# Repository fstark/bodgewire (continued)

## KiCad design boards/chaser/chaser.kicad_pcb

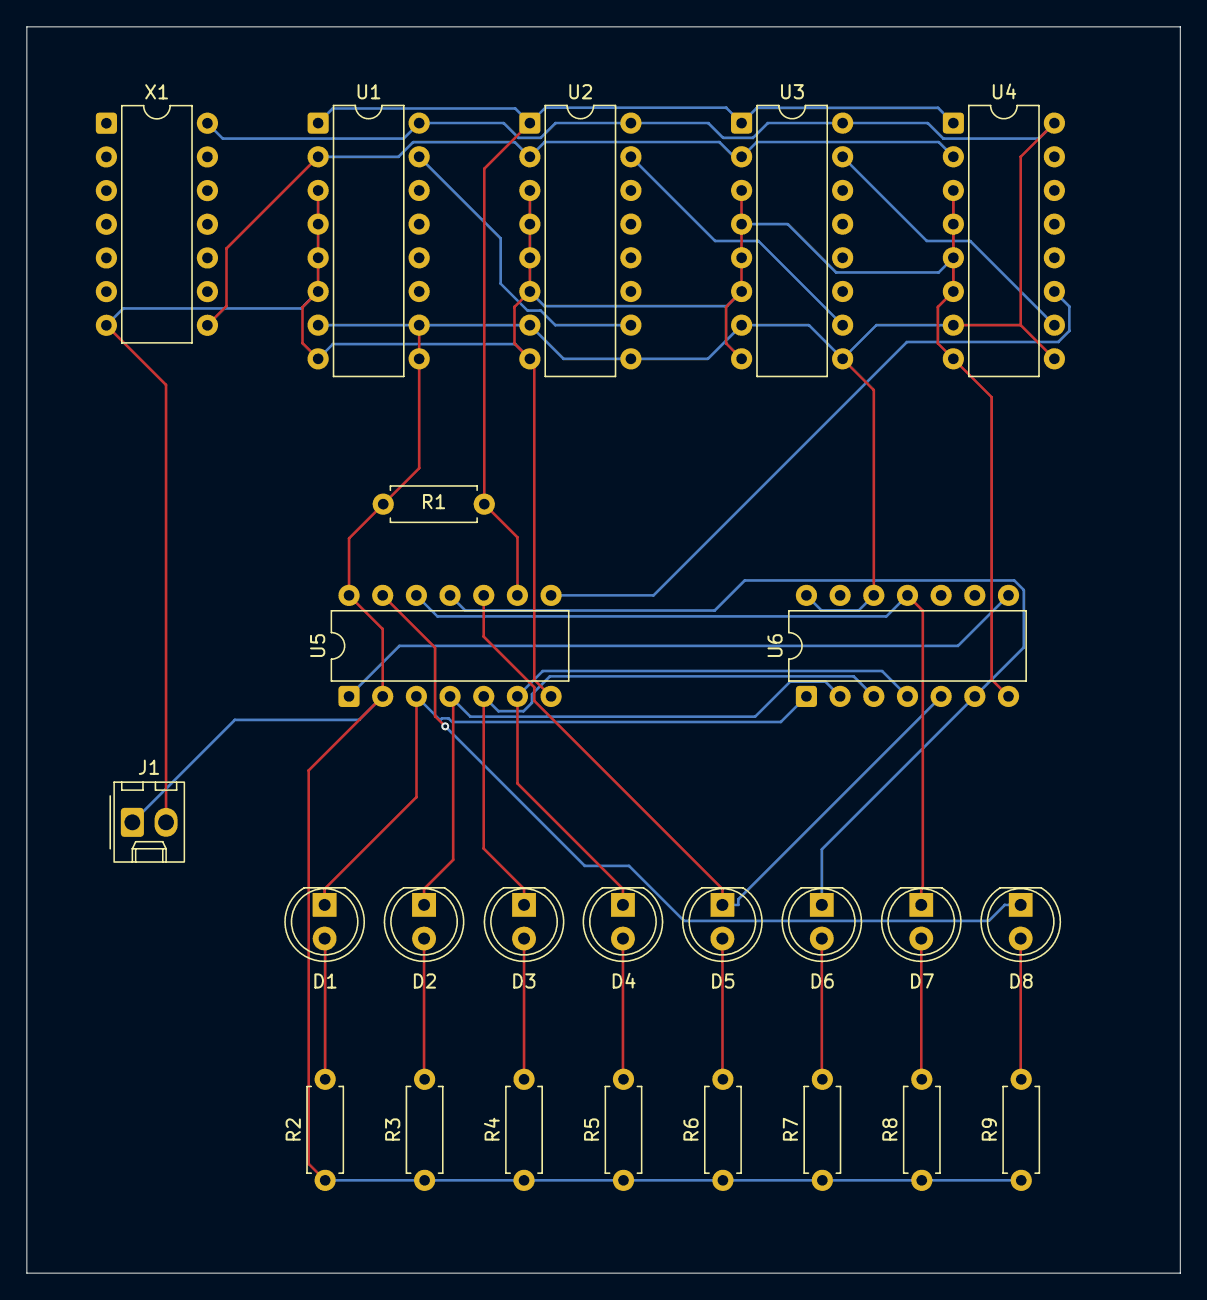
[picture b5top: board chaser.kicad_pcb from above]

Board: 2 copper layers, 87.0 x 94.0 mm, 25 parts (0 on the bottom side), 25 nets.

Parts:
D1, D2, D3, D4, D5, D6, D7, D8: LED; LED_D5.0mm
J1: POWER; Molex_KK-254_AE-6410-02A_1x02_P2.54mm_Vertical
R1: 4k7; R_Axial_DIN0207_L6.3mm_D2.5mm_P7.62mm_Horizontal
R2, R3, R4, R5, R6, R7, R8, R9: 330; R_Axial_DIN0207_L6.3mm_D2.5mm_P7.62mm_Horizontal
U1, U2, U3, U4: 74LS161; DIP-16_W7.62mm
U5: 74LS164; DIP-14_W7.62mm
U6: 74LS30; DIP-14_W7.62mm
X1: OSC; DIP-14_W7.62mm

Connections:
CARRY1: U1.15 (RCO), U2.10 (ENT)
CARRY2: U2.15 (RCO), U3.10 (ENT)
CARRY3: U3.15 (RCO), U4.10 (ENT)
CLK: U1.2 (CLK), U2.2 (CLK), U3.2 (CLK), U4.2 (CLK), X1.8 (OUT)
GND: J1.2 (GND), U1.3 (A), U1.4 (B), U1.5 (C), U1.6 (D), U1.8 (GND), U2.3 (A), U2.4 (B), U2.5 (C), U2.6 (D), U2.8 (GND), U3.3 (A), U3.4 (B), U3.5 (C), U3.6 (D), U3.8 (GND), U4.3 (A), U4.4 (B), U4.5 (C), U4.6 (D), U4.8 (GND), U5.7 (GND), U6.7 (GND), X1.7 (GND)
LED_A1: D1.2 (A), R2.2
LED_A2: D2.2 (A), R3.2
LED_A3: D3.2 (A), R4.2
LED_A4: D4.2 (A), R5.2
LED_A5: D5.2 (A), R6.2
LED_A6: D6.2 (A), R7.2
LED_A7: D7.2 (A), R8.2
LED_A8: D8.2 (A), R9.2
RESET_N: R1.2, U1.1 (CLR_N), U2.1 (CLR_N), U3.1 (CLR_N), U4.1 (CLR_N), U5.9 (CLR_N)
S1: D1.1 (K), U5.3 (QA), U6.1 (A)
S2: D2.1 (K), U5.4 (QB), U6.2 (B)
S3: D3.1 (K), U5.5 (QC), U6.3 (C)
S4: D4.1 (K), U5.6 (QD), U6.4 (D)
S5: D5.1 (K), U5.10 (QE), U6.5 (E)
S6: D6.1 (K), U5.11 (QF), U6.6 (F)
S7: D7.1 (K), U5.12 (QG), U6.11 (G)
S8: D8.1 (K), U5.13 (QH)
SER: U5.1 (A), U6.8 (Y)
STEP: U4.11 (QD), U5.8 (CLK)
VCC: J1.1 (VCC), R1.1, R2.1, R3.1, R4.1, R5.1, R6.1, R7.1, R8.1, R9.1, U1.7 (ENP), U1.9 (LOAD_N), U1.10 (ENT), U1.16 (VCC), U2.7 (ENP), U2.9 (LOAD_N), U2.16 (VCC), U3.7 (ENP), U3.9 (LOAD_N), U3.16 (VCC), U4.7 (ENP), U4.9 (LOAD_N), U4.16 (VCC), U5.2 (B), U5.14 (VCC), U6.12 (H), U6.14 (VCC), X1.14 (VCC)

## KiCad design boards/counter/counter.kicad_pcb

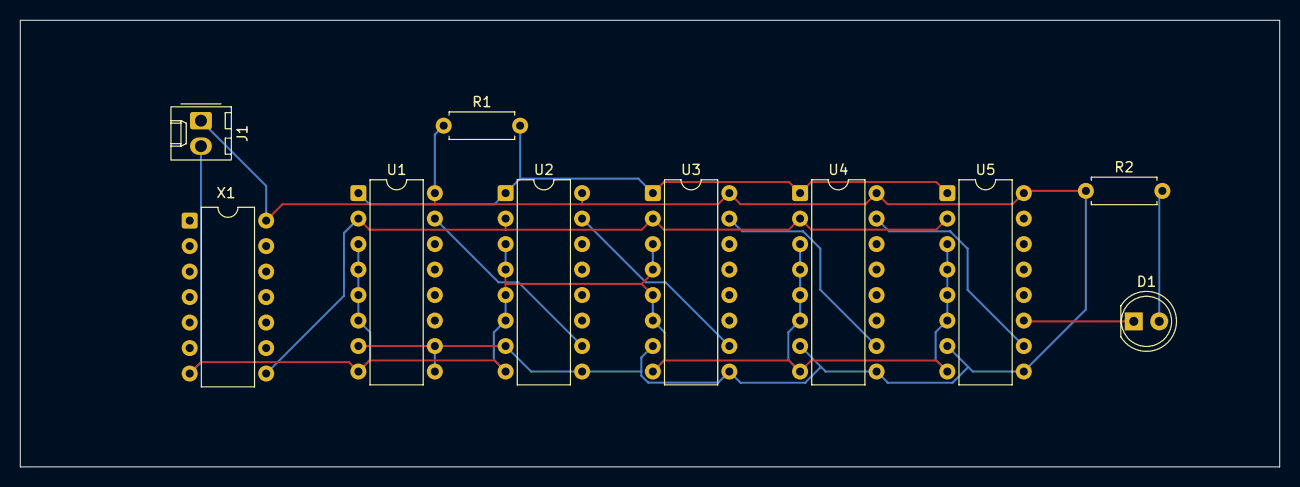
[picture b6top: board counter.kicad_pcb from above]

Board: 2 copper layers, 125.5 x 44.5 mm, 10 parts (0 on the bottom side), 10 nets.

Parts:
D1: LED; LED_D5.0mm
J1: POWER; Molex_KK-254_AE-6410-02A_1x02_P2.54mm_Vertical
R1: 4k7; R_Axial_DIN0207_L6.3mm_D2.5mm_P7.62mm_Horizontal
R2: 330; R_Axial_DIN0207_L6.3mm_D2.5mm_P7.62mm_Horizontal
U1, U2, U3, U4, U5: 74LS161; DIP-16_W7.62mm
X1: OSC; DIP-14_W7.62mm

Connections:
C19: D1.1 (K), U5.11 (QD)
CARRY1: U1.15 (RCO), U2.10 (ENT)
CARRY2: U2.15 (RCO), U3.10 (ENT)
CARRY3: U3.15 (RCO), U4.10 (ENT)
CARRY4: U4.15 (RCO), U5.10 (ENT)
CLK: U1.2 (CLK), U2.2 (CLK), U3.2 (CLK), U4.2 (CLK), U5.2 (CLK), X1.8 (OUT)
GND: J1.2 (GND), U1.3 (A), U1.4 (B), U1.5 (C), U1.6 (D), U1.8 (GND), U2.3 (A), U2.4 (B), U2.5 (C), U2.6 (D), U2.8 (GND), U3.3 (A), U3.4 (B), U3.5 (C), U3.6 (D), U3.8 (GND), U4.3 (A), U4.4 (B), U4.5 (C), U4.6 (D), U4.8 (GND), U5.3 (A), U5.4 (B), U5.5 (C), U5.6 (D), U5.8 (GND), X1.7 (GND)
LED_A: D1.2 (A), R2.2
RESET_N: R1.2, U1.1 (CLR_N), U2.1 (CLR_N), U3.1 (CLR_N), U4.1 (CLR_N), U5.1 (CLR_N)
VCC: J1.1 (VCC), R1.1, R2.1, U1.7 (ENP), U1.9 (LOAD_N), U1.10 (ENT), U1.16 (VCC), U2.7 (ENP), U2.9 (LOAD_N), U2.16 (VCC), U3.7 (ENP), U3.9 (LOAD_N), U3.16 (VCC), U4.7 (ENP), U4.9 (LOAD_N), U4.16 (VCC), U5.7 (ENP), U5.9 (LOAD_N), U5.16 (VCC), X1.14 (VCC)

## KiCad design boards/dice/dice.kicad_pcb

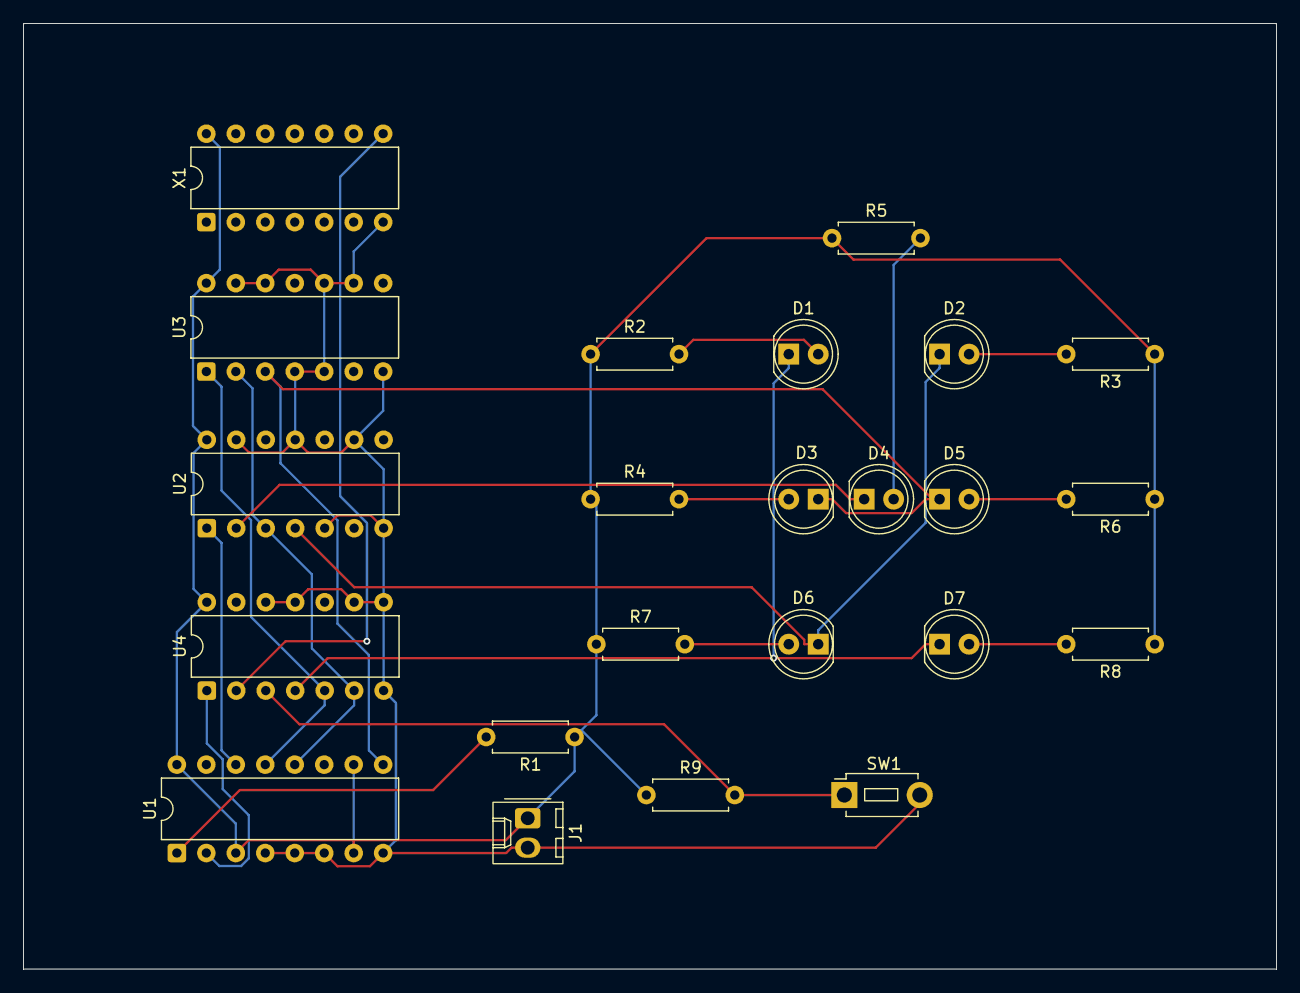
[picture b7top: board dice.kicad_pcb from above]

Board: 2 copper layers, 108.0 x 81.5 mm, 23 parts (0 on the bottom side), 20 nets.

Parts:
D1, D2, D3, D4, D5, D6, D7: LED; LED_D5.0mm
J1: POWER; Molex_KK-254_AE-6410-02A_1x02_P2.54mm_Vertical
R1, R9: 4k7; R_Axial_DIN0207_L6.3mm_D2.5mm_P7.62mm_Horizontal
R2, R3, R4, R5, R6, R7, R8: 330; R_Axial_DIN0207_L6.3mm_D2.5mm_P7.62mm_Horizontal
SW1: BUTTON; SW_PUSH_1P1T_6x3.5mm_H5.0_APEM_MJTP1250
U1: 74LS161; DIP-16_W7.62mm
U2: 74LS04; DIP-14_W7.62mm
U3: 74LS00; DIP-14_W7.62mm
U4: 74LS02; DIP-14_W7.62mm
X1: OSC; DIP-14_W7.62mm

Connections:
BTN_N: R9.2, SW1.1, U4.3 (1B)
CLK: U4.2 (1A), X1.8 (OUT)
FOUR_N: D2.1 (K), D6.1 (K), U2.4 (2Y)
GND: J1.2 (GND), SW1.2, U1.4 (B), U1.5 (C), U1.6 (D), U1.8 (GND), U2.5 (3A), U2.7 (GND), U2.9 (4A), U2.11 (5A), U2.13 (6A), U3.4 (2A), U3.5 (2B), U3.7 (GND), U3.9 (3A), U3.10 (3B), U3.12 (4A), U3.13 (4B), U4.7 (GND), U4.8 (3A), U4.9 (3B), U4.11 (4A), U4.12 (4B), X1.7 (GND)
LED_A1: D1.2 (A), R2.2
LED_A2: D2.2 (A), R3.2
LED_A3: D3.2 (A), R4.2
LED_A4: D4.2 (A), R5.2
LED_A5: D5.2 (A), R6.2
LED_A6: D6.2 (A), R7.2
LED_A7: D7.2 (A), R8.2
N0: U1.14 (QA), U2.1 (1A)
N1: U1.13 (QB), U3.1 (1A), U4.5 (2A)
N2: U1.12 (QC), U2.3 (2A), U3.2 (1B), U4.6 (2B)
ODD_N: D4.1 (K), U2.2 (1Y)
RESET_N: R1.2, U1.1 (CLR_N)
ROLL_CLK: U1.2 (CLK), U4.1 (1Y)
SIX_N: D3.1 (K), D5.1 (K), U1.9 (LOAD_N), U3.3 (1Y)
TWO_N: D1.1 (K), D7.1 (K), U4.4 (2Y)
VCC: J1.1 (VCC), R1.1, R2.1, R3.1, R4.1, R5.1, R6.1, R7.1, R8.1, R9.1, U1.3 (A), U1.7 (ENP), U1.10 (ENT), U1.16 (VCC), U2.14 (VCC), U3.14 (VCC), U4.14 (VCC), X1.14 (VCC)

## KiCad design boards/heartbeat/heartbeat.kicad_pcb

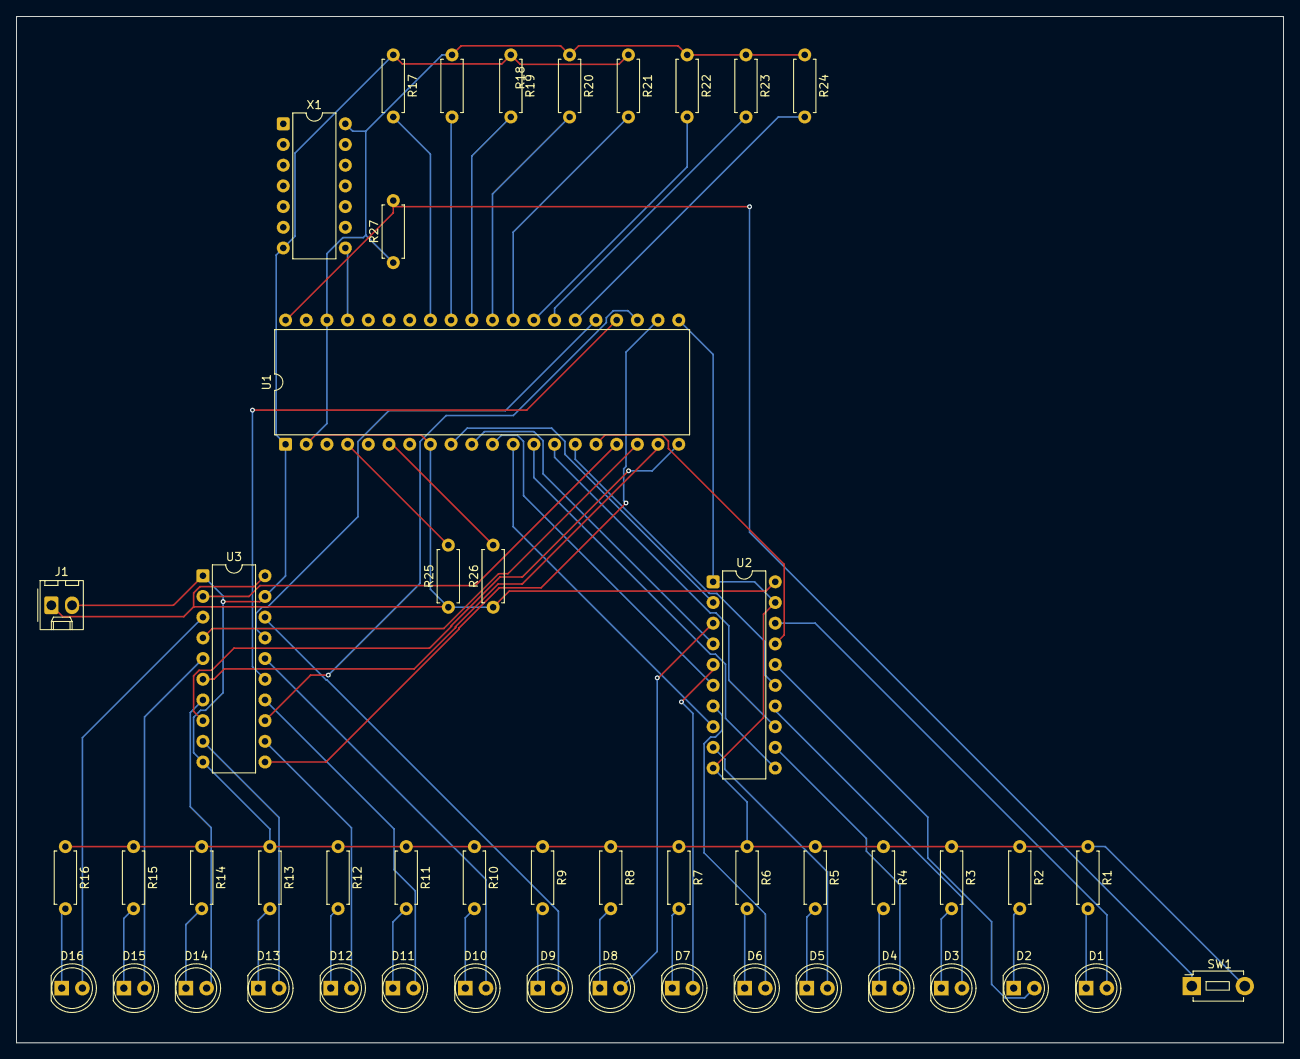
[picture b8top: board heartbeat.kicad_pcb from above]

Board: 2 copper layers, 155.5 x 126.0 mm, 49 parts (0 on the bottom side), 62 nets.

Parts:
D1, D2, D3, D4, D5, D6, D7, D8, D9, D10, D11, D12, D13, D14, D15, D16: LED; LED_D5.0mm
J1: POWER; Molex_KK-254_AE-6410-02A_1x02_P2.54mm_Vertical
R1, R2, R3, R4, R5, R6, R7, R8, R9, R10, R11, R12, R13, R14, R15, R16: 330; R_Axial_DIN0207_L6.3mm_D2.5mm_P7.62mm_Horizontal
R17, R18, R19, R20, R21, R22, R23, R24, R27: 4k7; R_Axial_DIN0207_L6.3mm_D2.5mm_P7.62mm_Horizontal
R25, R26: 3k3; R_Axial_DIN0207_L6.3mm_D2.5mm_P7.62mm_Horizontal
SW1: BUTTON; SW_PUSH_1P1T_6x3.5mm_H5.0_APEM_MJTP1250
U1: 6502; DIP-40_W15.24mm
U2, U3: 74LS244; DIP-20_W7.62mm
X1: OSC; DIP-14_W7.62mm

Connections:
A0: U1.9 (A0), U2.2 (1A1)
A1: U1.10 (A1), U2.4 (1A2)
A2: U1.11 (A2), U2.6 (1A3)
A3: U1.12 (A3), U2.8 (1A4)
A4: U1.13 (A4), U2.11 (2A1)
A5: U1.14 (A5), U2.13 (2A2)
A6: U1.15 (A6), U2.15 (2A3)
A7: U1.16 (A7), U2.17 (2A4)
A8: U1.17 (A8), U3.2 (1A1)
A9: U1.18 (A9), U3.4 (1A2)
A10: U1.19 (A10), U3.6 (1A3)
A11: U1.20 (A11), U3.8 (1A4)
A12: U1.22 (A12), U3.11 (2A1)
A13: U1.23 (A13), U3.13 (2A2)
A14: U1.24 (A14), U3.15 (2A3)
A15: U1.25 (A15), U3.17 (2A4)
DB0: R17.2, U1.33 (D0)
DB1: R18.2, U1.32 (D1)
DB2: R19.2, U1.31 (D2)
DB3: R20.2, U1.30 (D3)
DB4: R21.2, U1.29 (D4)
DB5: R22.2, U1.28 (D5)
DB6: R23.2, U1.27 (D6)
DB7: R24.2, U1.26 (D7)
GND: J1.2 (GND), R1.1, R2.1, R3.1, R4.1, R5.1, R6.1, R7.1, R8.1, R9.1, R10.1, R11.1, R12.1, R13.1, R14.1, R15.1, R16.1, R17.1, R19.1, R21.1, SW1.2, U1.1 (GND), U1.21 (GND2), U2.1 (1OE_N), U2.10 (GND), U2.19 (2OE_N), U3.1 (1OE_N), U3.10 (GND), U3.19 (2OE_N), X1.7 (GND)
IRQ_N: R25.2, U1.4 (IRQ_N)
LA0: D1.2 (A), U2.18 (1Y1)
LA1: D2.2 (A), U2.16 (1Y2)
LA2: D3.2 (A), U2.14 (1Y3)
LA3: D4.2 (A), U2.12 (1Y4)
LA4: D5.2 (A), U2.9 (2Y1)
LA5: D6.2 (A), U2.7 (2Y2)
LA6: D7.2 (A), U2.5 (2Y3)
LA7: D8.2 (A), U2.3 (2Y4)
LA8: D9.2 (A), U3.18 (1Y1)
LA9: D10.2 (A), U3.16 (1Y2)
LA10: D11.2 (A), U3.14 (1Y3)
LA11: D12.2 (A), U3.12 (1Y4)
LA12: D13.2 (A), U3.9 (2Y1)
LA13: D14.2 (A), U3.7 (2Y2)
LA14: D15.2 (A), U3.5 (2Y3)
LA15: D16.2 (A), U3.3 (2Y4)
LK0: D1.1 (K), R1.2
LK1: D2.1 (K), R2.2
LK2: D3.1 (K), R3.2
LK3: D4.1 (K), R4.2
LK4: D5.1 (K), R5.2
LK5: D6.1 (K), R6.2
LK6: D7.1 (K), R7.2
LK7: D8.1 (K), R8.2
LK8: D9.1 (K), R9.2
LK9: D10.1 (K), R10.2
LK10: D11.1 (K), R11.2
LK11: D12.1 (K), R12.2
LK12: D13.1 (K), R13.2
LK13: D14.1 (K), R14.2
LK14: D15.1 (K), R15.2
LK15: D16.1 (K), R16.2
NMI_N: R26.2, U1.6 (NMI_N)
PHI0: U1.37 (PHI0), X1.8 (OUT)
RES_N: R27.2, SW1.1, U1.40 (RES_N)
VCC: J1.1 (VCC), R18.1, R20.1, R22.1, R23.1, R24.1, R25.1, R26.1, R27.1, U1.2 (RDY), U1.8 (VCC), U1.38 (SO), U2.20 (VCC), U3.20 (VCC), X1.14 (VCC)
